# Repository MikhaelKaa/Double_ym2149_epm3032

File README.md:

# TurboSound #

### --- ###

* Две YM2149
* Логика выборки в epm3032
* Covox на КР572ПА1А

## Вариант реализации в виде печатной платы:

Автор трассировки.
https://github.com/ponchick/TS_Ext_EPM3032

### Версия прошивки для платы 1.5 без каких либо доработок:
/docs/1.5fix/EPM3032_ponchick_ver1.5.pof

### Версия прошивки для 1.5 с доработками:
/docs/1.5fix/EPM3032_ponchick_ver1.5fix.pof

## Макет с ковоксом:

В планах: добавить цифровую регулировку громкости.

Идеи и предложения принимаются.

## Благодарности:

Михаил Андреев ака Микка - за тесты карточки.

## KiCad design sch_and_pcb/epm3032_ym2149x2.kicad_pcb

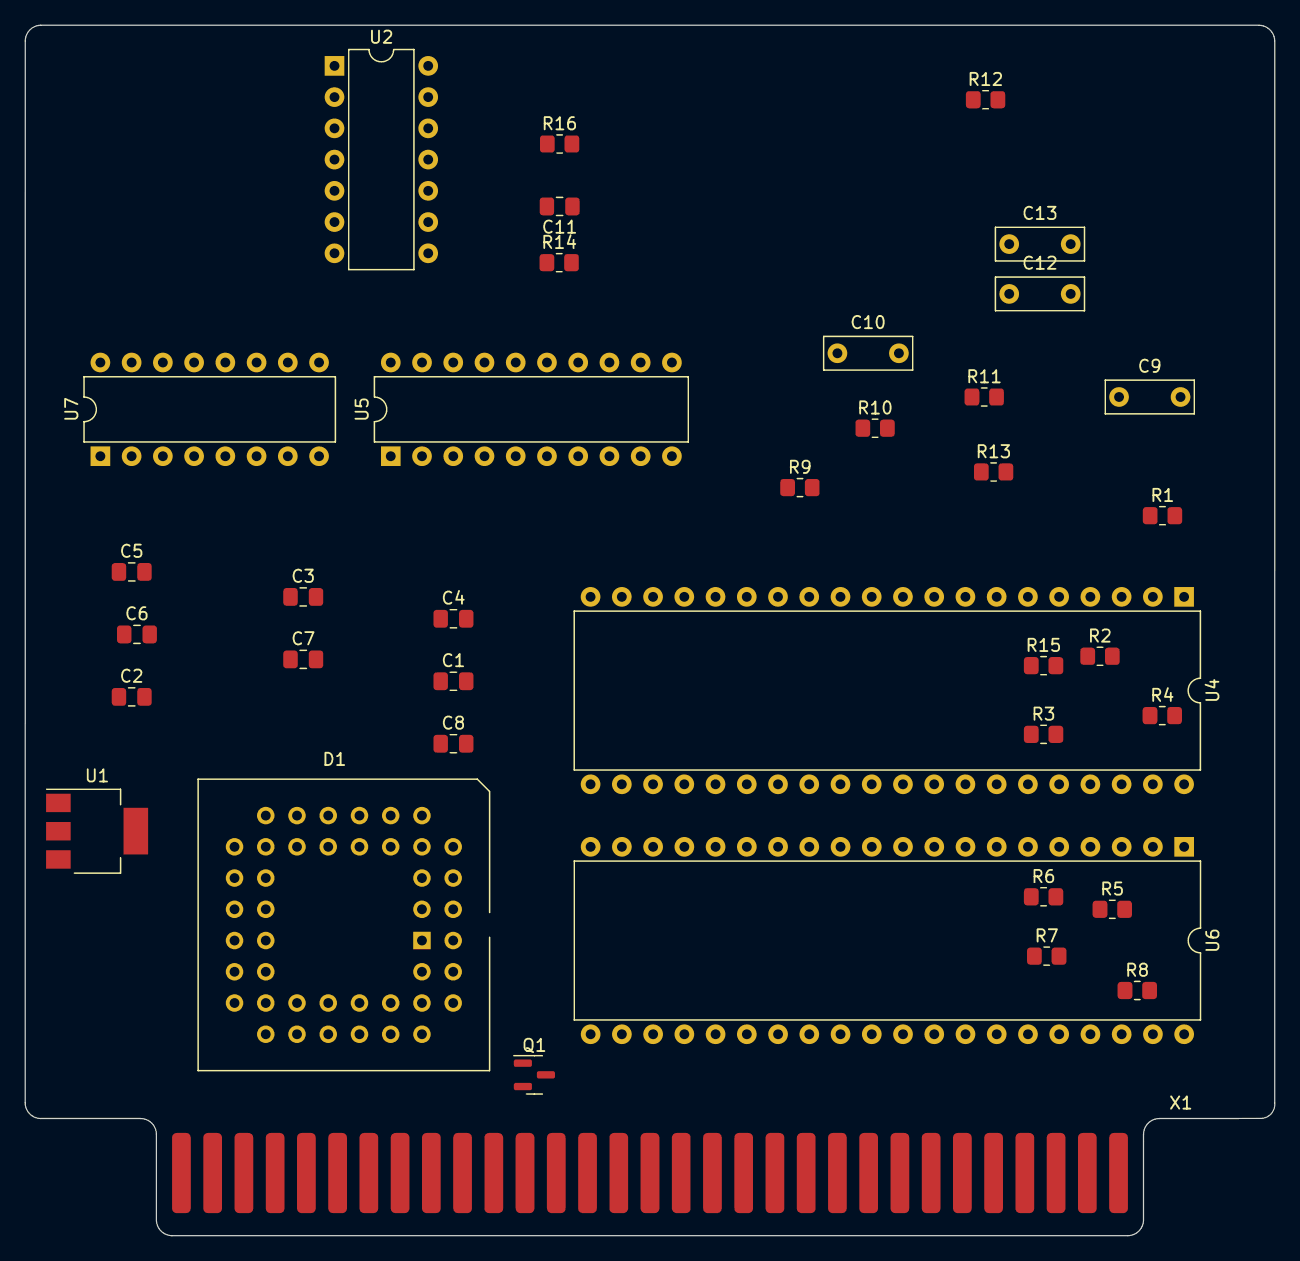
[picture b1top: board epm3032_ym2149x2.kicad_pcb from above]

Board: 2 copper layers, 101.6 x 98.4 mm, 38 parts (0 on the bottom side), 50 nets, no tracks yet.

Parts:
C1: 10uF10VX7R0805; C_0805_2012Metric_Pad1.18x1.45mm_HandSolder
C2, C3, C4, C5, C6, C7, C8, C11: 0.47uF50VX7R0805; C_0805_2012Metric_Pad1.18x1.45mm_HandSolder
C9, C10, C12, C13: 0.47uF wima; C_Rect_L7.0mm_W2.5mm_P5.00mm
D1: epm3032; PLCC-44_THT-Socket
Q1: BC847; SOT-23
R1, R4, R5, R8: 4.7K; R_0805_2012Metric_Pad1.20x1.40mm_HandSolder
R2, R3, R6, R7, R11, R12, R13, R14, R15, R16: 10K; R_0805_2012Metric_Pad1.20x1.40mm_HandSolder
R9, R10: 1K; R_0805_2012Metric_Pad1.20x1.40mm_HandSolder
U1: AMS1117-3.3; SOT-223-3_TabPin2
U2: LM324; DIP-14_W7.62mm
U4, U6: YM2149; DIP-40_W15.24mm
U5: 74HC374; DIP-20_W7.62mm
U7: AD7533JN; DIP-16_W7.62mm
X1: zx-bus

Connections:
/+3.3V: C2.1, C4.1, C6.1, C7.1, U1.2 (VO)
/+5V: C1.1, C3.1, C5.1, C8.1, Q1.3 (C), R16.1, U1.3 (VI), U2.4 (V+), U4.28 (BC2), U4.40 (VCC), U6.28 (BC2), U6.40 (VCC)
/GND: C1.2, C2.2, C3.2, C4.2, C5.2, C6.2, C7.2, C8.2, C11.2, D1.10 (gnd), R9.1, R10.1, R14.1, U1.1 (GND), U2.11 (V-), U4.1 (VSS), U4.24 (~A9), U6.1 (VSS), U6.24 (~A9), X1.29 (GND), X1.37 (GND), X1.38 (GND), X1.45 (GND), X1.61 (GND)
/IOGE: Q1.2 (E), X1.44 (IOGE)
/YM_0_A: R1.1, U4.3 (A)
/YM_0_B: R2.1, R3.1, U4.4 (B)
/YM_0_C: R4.1, U4.38 (C)
/YM_1_A: R5.1, U6.3 (A)
/YM_1_B: R6.1, R7.1, U6.4 (B)
/YM_1_C: R8.1, U6.38 (C)
/a0: D1.11 (io), X1.40 (A0)
/a1: D1.9 (io), X1.41 (A1)
/a8_0: D1.19 (io), U4.25 (A8)
/a8_1: D1.20 (io), U6.25 (A8)
/a14: D1.29 (io), X1.2 (A13)
/a15: D1.31 (io), X1.1 (A15)
/bc1: D1.16 (io), U4.29 (BC1), U6.29 (BC1)
/bdir: D1.14 (io), U4.27 (BDIR), U6.27 (BDIR)
/clk175: D1.18 (io), U4.22 (CLOCK), U6.22 (CLOCK)
/clk350: D1.43 (clk), X1.39 (3.5)
/d0: D1.34 (io), U4.37 (DA0), U6.37 (DA0), X1.6 (D0)
/d1: D1.28 (io), U4.36 (DA1), U6.36 (DA1), X1.7 (D1)
/d2: U4.35 (DA2), U6.35 (DA2), X1.8 (D2)
/d3: D1.41 (io), U4.34 (DA3), U6.34 (DA3), X1.11 (D3)
/d4: D1.5 (io), U4.33 (DA4), U6.33 (DA4), X1.12 (D4)
/d5: D1.40 (io), U4.32 (DA5), U6.32 (DA5), X1.10 (D5)
/d6: D1.39 (io), U4.31 (DA6), U6.31 (DA6), X1.9 (D6)
/d7: D1.33 (io), U4.30 (DA7), U6.30 (DA7), X1.3 (D7)
/ioge_c: D1.27 (io), Q1.1 (B)
/iorq: D1.6 (io), X1.17 (IORQ)
/m1: D1.8 (io), X1.23 (M1)
/reset: D1.4 (io), U4.23 (~RESET), U6.23 (~RESET), X1.51 (RES)
/wr: D1.12 (io), X1.18 (RD)
unnamed: C9.1, R1.2, R2.2, R5.2, R6.2, R9.2
unnamed: C9.2, R11.1
unnamed: C10.1, R12.1
unnamed: C10.2, R3.2, R4.2, R7.2, R8.2, R10.2
unnamed: C11.1, R14.2, R16.2, U2.10 (+), U2.12 (+)
unnamed: C12.1, R13.2, U2.8
unnamed: C13.2, R15.2, U2.14
unnamed: R11.2, R13.1, U2.9 (-)
unnamed: R12.2, R15.1, U2.13 (-)
unnamed: U5.2 (O0), U7.4 (D9(MSB))
unnamed: U5.5 (O1), U7.5 (D8)
unnamed: U5.6 (O2), U7.6 (D7)
unnamed: U5.9 (O3), U7.7 (D6)
unnamed: U5.12 (O4), U7.8 (D5)
unnamed: U5.15 (O5), U7.9 (D4)
unnamed: U5.16 (O6), U7.10 (D3)
unnamed: U5.19 (O7), U7.11 (D2)

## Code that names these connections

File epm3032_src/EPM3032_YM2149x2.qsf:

# -------------------------------------------------------------------------- #
#
# Copyright (C) 1991-2013 Altera Corporation
# Your use of Altera Corporation's design tools, logic functions 
# and other software and tools, and its AMPP partner logic 
# functions, and any output files from any of the foregoing 
# (including device programming or simulation files), and any 
# associated documentation or information are expressly subject 
# to the terms and conditions of the Altera Program License 
# Subscription Agreement, Altera MegaCore Function License 
# Agreement, or other applicable license agreement, including, 
# without limitation, that your use is for the sole purpose of 
# programming logic devices manufactured by Altera and sold by 
# Altera or its authorized distributors.  Please refer to the 
# applicable agreement for further details.
#
# -------------------------------------------------------------------------- #
#
# Quartus II 64-Bit
# Version 13.0.1 Build 232 06/12/2013 Service Pack 1 SJ Web Edition
# Date created = 20:15:30  May 20, 2022
#
# -------------------------------------------------------------------------- #
#
# Notes:
#
# 1) The default values for assignments are stored in the file:
#		EPM3032_YM2149x2_assignment_defaults.qdf
#    If this file doesn't exist, see file:
#		assignment_defaults.qdf
#
# 2) Altera recommends that you do not modify this file. This
#    file is updated automatically by the Quartus II software
#    and any changes you make may be lost or overwritten.
#
# -------------------------------------------------------------------------- #


set_global_assignment -name FAMILY MAX3000A
set_global_assignment -name DEVICE "EPM3032ALC44-10"
set_global_assignment -name TOP_LEVEL_ENTITY EPM3032_YM2149x2
set_global_assignment -name ORIGINAL_QUARTUS_VERSION "13.0 SP1"
set_global_assignment -name PROJECT_CREATION_TIME_DATE "20:15:30  MAY 20, 2022"
set_global_assignment -name LAST_QUARTUS_VERSION "13.0 SP1"
set_global_assignment -name PROJECT_OUTPUT_DIRECTORY output_files
set_global_assignment -name ERROR_CHECK_FREQUENCY_DIVISOR "-1"
set_global_assignment -name VERILOG_FILE EPM3032_YM2149x2.v
set_global_assignment -name MAX7000_DEVICE_IO_STANDARD "3.3-V LVTTL"
set_location_assignment PIN_9 -to a1
set_location_assignment PIN_29 -to a14
set_location_assignment PIN_31 -to a15
set_location_assignment PIN_16 -to bc1
set_location_assignment PIN_14 -to bdir
set_location_assignment PIN_6 -to iorq
set_location_assignment PIN_8 -to m1
set_location_assignment PIN_12 -to wr
set_location_assignment PIN_11 -to a0
set_location_assignment PIN_21 -to beeper
set_location_assignment PIN_24 -to tapeout
set_location_assignment PIN_4 -to reset
set_location_assignment PIN_27 -to ioge_c
set_location_assignment PIN_44 -to a2
set_location_assignment PIN_25 -to covox
set_location_assignment PIN_34 -to d_0
set_location_assignment PIN_41 -to d_3
set_location_assignment PIN_5 -to d_4
set_location_assignment PIN_40 -to d_5
set_location_assignment PIN_39 -to d_6
set_location_assignment PIN_33 -to d_7
set_location_assignment PIN_43 -to cpu_clock
set_location_assignment PIN_18 -to ym_clock
set_location_assignment PIN_19 -to ym_0
set_location_assignment PIN_20 -to ym_1
set_location_assignment PIN_37 -to rd
set_location_assignment PIN_26 -to a3
set_location_assignment PIN_28 -to a13
set_global_assignment -name TIMEQUEST_MULTICORNER_ANALYSIS OFF
set_global_assignment -name SMART_RECOMPILE ON
set_global_assignment -name OPTIMIZE_HOLD_TIMING OFF
set_global_assignment -name OPTIMIZE_MULTI_CORNER_TIMING OFF
set_global_assignment -name FITTER_EFFORT "STANDARD FIT"
set_location_assignment PIN_1 -to div2
set_location_assignment PIN_2 -to interrupt

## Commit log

2022-07-05 >> пусть будет...
2022-07-06 >> продолжаем продолжать. Макетка рулез.
2022-08-10 >> прототип на макетке поет
2022-10-03 >> d7 33 to 26 pin
2022-11-09 >> auto detect and division cpu clock 3.5/7 MHz for YM.
2022-11-12 >> добавил сигнал dos, нужно тестировать.
2023-10-09 >> Эксперементы.
2023-10-11 >> Добавлены в gitignore файлы backups KiCad
2023-10-11 >> Добавлена заготовка под testbench.
2023-10-11 >> Эксперименты на тему определения турбо режима. Пока успехов нет.
2023-10-14 >> Все сломалось и не работает.
2023-10-14 >> Добавил в тест примеры. Вывод по условию и ожидание событий.
2024-04-17 >> Исправления в коде CPLD.
2024-04-18 >>Вариант дешифрации с rd
2024-05-01 >> После сброса активен первый чип.
2024-11-15 fix: README.md добавил репу с печатной платой.
2024-11-28 add: Первый запуск версии 1.5
2024-11-28 add: предупреждение о баге.
2024-11-29 todo: доделать tb.v
2024-11-29 test: 0xbffd TB
2024-11-30 add: Версия 1.5fix
2024-12-07 fix: Старая версия оставлена как исторический артефакт.
2024-12-07 fix: Версия прошивки. Железо 1.5fix. Нужно тестировать.
2024-12-07 fix: теперь iorqge чуть раньше iorq.
2024-12-08 add: Прошивка под 1.5fix для GMX. Добавлен сигнал int для детекта турбы.
2024-12-08 fix: Исправленная версия прошивки для 1.5fix.
2024-12-11 fix: Дополнил инструкции.
2024-12-11 init: Ветка с прошивкой для П2.2, пока остановлено - нет надежного железа ТС
